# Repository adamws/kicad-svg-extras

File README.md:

<div align="center">

# kicad-svg-extras

_Generate colored SVG files from KiCad PCB files with advanced styling options._

</div>

## Motivation

The `kicad-svg-extras` tool extends KiCad's built-in SVG export capabilities by adding support for custom net colors, CSS-based styling, and advanced color management. While `kicad-cli` provides basic SVG export, this tool respects per-net color settings defined in your PCB project and offers flexible styling options for web integration.

<table>
    <tr>
        <td colspan="2" align="center"></td>
    </tr>
    <tr>
        <td style="width:50%" align="center"><b>kicad-svg-extras</b></td>
        <td style="width:50%" align="center"><b>kicad-cli pcb export svg</b></td>
    </tr>
    <tr>
        <td align="center"></td>
        <td align="center"></td>
    </tr>
</table>

## Features

1. 🎨 **Color-Aware SVG Generation**
    - **Project Color Integration**: Automatically reads and applies net colors from your KiCad project file
    - **Custom Color Override**: Set specific colors for individual nets via command line or JSON configuration
1. 🌐 **Web-Ready CSS Styling**
    - **CSS Class Generation**: Generate SVGs with CSS classes for each net
    - **Metadata Export**: Export CSS class mappings for easy integration
    - **[Live Interactive Demo](https://adamws.github.io/kicad-svg-extras/)**: Try the web features online
1. ⚙️ **Extra Options**
    - **Fit-to-Content**: Automatic canvas sizing based on board edges
    - **Zone Control**: Option to include or exclude copper zones
    - **Background Customization**: Set custom background colors instead of transparent backgrounds

## Installation

### Recommended: Using pipx (Preferred)

[pipx](https://pipx.pypa.io/) is the recommended way to install Python CLI tools.
It installs the tool in an isolated environment while making it globally available:

```bash
pipx install git+https://github.com/adamws/kicad-svg-extras.git
```

For one-time runs use [uvx](https://docs.astral.sh/uv/concepts/tools/):

```bash
uvx --from git+https://github.com/adamws/kicad-svg-extras.git kicad-svg-extras --help
```

**Requirements:**
- KiCad (with Python bindings)
- Python 3.8+

The tool automatically detects and imports KiCad's `pcbnew` module from common installation locations,
so it works in isolated environments without special configuration.

### Custom KiCad Installation Path

If KiCad is installed in a non-standard location, you can specify the path to the pcbnew module
using the `KICAD_PCBNEW_PATH` environment variable:

```bash
export KICAD_PCBNEW_PATH="/path/to/kicad/python/site-packages"
kicad-svg-extras --output board.svg board.kicad_pcb
```

When this environment variable is set, the tool will use it exclusively and will not fall back
to automatic discovery if the path is invalid.

## Usage

<table>
<tr>
<th colspan="2"><b>Basic Usage - Project Colors</b></th>
</tr>
<tr>
<td>

Generate an SVG using colors defined in your KiCad project:

```bash
kicad-svg-extras --output board.svg board.kicad_pcb
```

This automatically:
- Detects the corresponding `.kicad_pro` file
- Applies net colors from the project's `net_colors` settings
- Processes default layers (F.Cu, B.Cu)

</td>
<td>

</td>
</tr>
<tr>
<th colspan="2"><b>Custom Net Colors</b></th>
</tr>
<tr>
<td>

Override specific net colors from the command line
and via `color.json` definition.

```bash
kicad-svg-extras --output board.svg --layers "B.Cu" \
  --ignore-project-colors \
  --net-color "VCC:#fabd2f" --colors colors.json \
  board.kicad_pcb
```

**Supported color formats:**
- Hex: `#FF0000`, `#f00`
- RGB: `rgb(255,0,0)`
- Named: `red`, `green`, `blue`

**colors.json example:**

```json
{
  "net_colors": {
    "N$*": "#b8bb26",
    "VCC": "black",
    "GND": "gray"
  }
}
```

Net names in both `--net-color` and `--colors` json file support wildcards.

</td>
<td>

</td>
</tr>
<tr>
<th colspan="2"><b>CSS Mode for Web Integration</b></th>
</tr>
<tr>
<td>

Generate web-ready SVGs with CSS classes:

```bash
kicad-svg-extras --output board.svg \
  --ignore-project-colors \
  --use-css-classes \
  --export-metadata metadata.json \
  board.kicad_pcb
```

**Creates:**
- **board.svg**: SVG with CSS classes like `.net-gnd-f-cu`
- **metadata.json**: Net-to-CSS mappings

</td>
<td>

</b>
**[Live Interactive Demo](https://adamws.github.io/kicad-svg-extras/)**

</td>
</tr>
</table>

## Command Line Reference

**Basic Syntax:** `kicad-svg-extras -o OUTPUT_FILE [OPTIONS] PCB_FILE`

<table>
<tr>
<th colspan="2"><b>Required Arguments</b></th>
</tr>
<tr>
<td><code>PCB_FILE</code></td>
<td>Input KiCad PCB file (<code>.kicad_pcb</code>)</td>
</tr>
<tr>
<td><code>-o, --output OUTPUT_FILE</code></td>
<td>Output SVG file path</td>
</tr>
<tr>
<th colspan="2"><b>Color Configuration</b></th>
</tr>
<tr>
<td><code>--net-color NET_NAME:COLOR</code></td>
<td>Set color for specific net. Format: <code>net_name:color</code>. Can be used multiple times. Supports hex (<code>#FF0000</code>), RGB (<code>rgb(255,0,0)</code>), or named colors (<code>red</code>).</td>
</tr>
<tr>
<td><code>--colors CONFIG_FILE</code></td>
<td>JSON file with net name to color mapping</td>
</tr>
<tr>
<td><code>--ignore-project-colors</code></td>
<td>Ignore net colors defined in the KiCad project file</td>
</tr>
<tr>
<td><code>-t, --theme THEME_NAME</code></td>
<td>Color theme to use (defaults to PCB editor settings if theme not found)</td>
</tr>
<tr>
<th colspan="2"><b>Layer Selection</b></th>
</tr>
<tr>
<td><code>--layers LAYERS</code></td>
<td>Comma-separated list of KiCad layer names to process (e.g., <code>F.Cu,B.Cu,In1.Cu,In2.Cu</code> or <code>F.Cu,F.SilkS,Edge.Cuts</code>). Default: <code>F.Cu,B.Cu</code></td>
</tr>
<tr>
<th colspan="2"><b>Output Options</b></th>
</tr>
<tr>
<td><code>--use-css-classes</code></td>
<td>Use CSS classes for styling instead of hardcoded colors. Generates individual SVG per net (slower) but allows easy color customization via CSS. Classes: <code>.net-&lt;name&gt; { fill: color; }</code></td>
</tr>
<tr>
<td><code>--export-metadata METADATA_FILE</code></td>
<td>Export net name to CSS class mapping metadata to JSON file. Only useful with <code>--use-css-classes</code>. Contains mapping of actual net names to their CSS class names for integration purposes.</td>
</tr>
<tr>
<td><code>--fit-to-content {none,all,edges_only}</code></td>
<td>Control how bounding box is calculated: <code>none</code> disables fitting (keeps original canvas), <code>all</code> uses all PCB components, <code>edges_only</code> uses only board edges (default)</td>
</tr>
<tr>
<td><code>--no-background</code></td>
<td>Do not add a background to the output SVGs</td>
</tr>
<tr>
<td><code>--background-color BACKGROUND_COLOR</code></td>
<td>Background color for the output SVGs (default: <code>#FFFFFF</code>)</td>
</tr>
<tr>
<th colspan="2"><b>PCB Content Options</b></th>
</tr>
<tr>
<td><code>--skip-zones</code></td>
<td>Skip drawing zones in the output SVGs</td>
</tr>
<tr>
<th colspan="2"><b>Development & Debugging</b></th>
</tr>
<tr>
<td><code>--keep-intermediates</code></td>
<td>Keep intermediate files for debugging</td>
</tr>
<tr>
<td><code>--log-level {DEBUG,INFO,WARNING,ERROR,CRITICAL}</code></td>
<td>Set the logging level (default: INFO)</td>
</tr>
</table>

**Examples**

```bash
# Basic usage with project colors
kicad-svg-extras --output board.svg board.kicad_pcb
# Custom net colors
kicad-svg-extras --output board.svg --net-color 'GND:green' --net-color 'VCC:red' board.kicad_pcb
# Wildcard net patterns
kicad-svg-extras --output board.svg --net-color 'SIGNAL*:blue' board.kicad_pcb
# Using color configuration file
kicad-svg-extras --output board.svg --colors colors.json board.kicad_pcb
# CSS mode for web integration
kicad-svg-extras --output board.svg --use-css-classes --export-metadata metadata.json board.kicad_pcb
# Custom layers and background
kicad-svg-extras --output board.svg --layers "F.Cu,F.SilkS,Edge.Cuts" --background-color "#000000" board.kicad_pcb
# Fit to board edges only, skip zones
kicad-svg-extras --output board.svg --fit-to-content edges_only --skip-zones board.kicad_pcb
```

## How It Works

### Color Priority System

Colors are resolved using a clear priority hierarchy:

1. CLI Arguments (Highest Priority)
2. JSON Configuration File
3. KiCad Project File
4. KiCad Theme Defaults (Lowest Priority)

### Processing Workflow

1. **Net Analysis**: Extract all nets from the PCB and determine which layers they appear on
2. **Color Resolution**: Apply the color priority system to assign final colors
3. **PCB Splitting**: Create filtered PCB files for each net group (same color nets are processed together)
4. **SVG Generation**: Use KiCad's plotting API to generate individual SVGs
5. **Color Application**: Apply colors either as direct fill attributes or CSS classes
6. **Layer Merging**: Combine all layers in the correct stacking order

## Development

### Running Tests

```bash
# Unit tests (no KiCad's pcbnew module required)
hatch run test-unit
# Functional tests (requires KiCad's pcbnew module)
hatch run test-functional
```

## Disclaimer

This project has been mostly AI generated using [claude-code](https://github.com/anthropics/claude-code).

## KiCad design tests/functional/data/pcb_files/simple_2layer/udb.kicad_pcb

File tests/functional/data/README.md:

# Test Data Directory

This directory contains test data for functional testing of kicad-svg-extras.

## Structure

```
tests/data/
├── pcb_files/          # KiCad PCB files for testing
│   ├── simple_2layer/  # Basic 2-layer board
│   ├── simple_4layer/  # Basic Multi-layer board
├── config_files/       # Color configuration files
│   ├── basic_colors.json      # Simple net color mappings
│   └── advanced_nets.json     # Complex patterns and wildcards
└── README.md          # This file
```

## PCB Files (To be added)

PCB test files should be organized by complexity and layer count:

- **simple_2layer/**: Basic 2-layer board
  - origins in [kle2netlist](https://github.com/adamws/kle2netlist)
- **simple_4layer/**: Basic Multi-layer board
  - copied from [UDB-C-EZM](https://github.com/Unified-Daughterboard/UDB-C-EZM)

## Configuration Files

### basic_colors.json
Simple color mappings for common nets:
- GND: Red (#FF0000)
- VCC: Blue (#0000FF)
- 3V3: Green (#00FF00)
- Plus wildcard patterns for DATA*, CLK*, etc.

### advanced_nets.json
Complex configuration with:
- Named colors (red, blue, green)
- Wildcard patterns (USB_*, SPI_*, I2C_*)
- KiCad project format compatibility

## Usage

These files are used by functional tests in `tests/functional/` to:
1. Generate SVG outputs with various CLI options
2. Compare against human-verified reference files
3. Test different layer combinations and color schemes
4. Validate error handling with invalid inputs

## Adding New Test Data

When adding new PCB files:
1. Place in appropriate subdirectory by complexity
2. Include a brief description of the board purpose
3. Generate reference SVG files using current tool version
4. Manually verify reference outputs before committing
5. Add corresponding test cases in functional tests

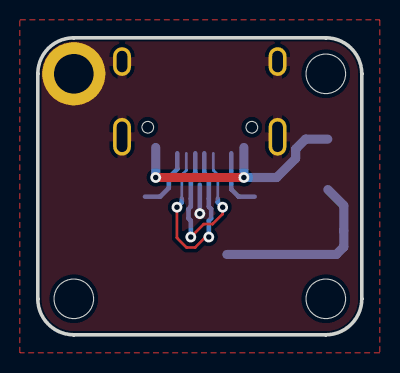
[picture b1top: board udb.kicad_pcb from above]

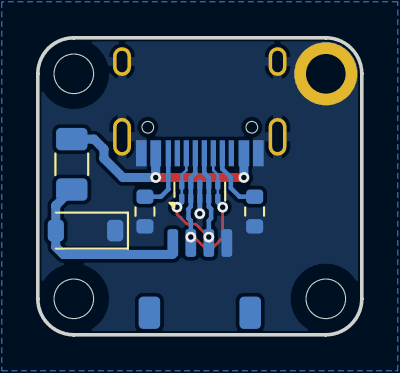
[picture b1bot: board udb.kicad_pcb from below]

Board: 2 copper layers, 18.0 x 16.5 mm, 11 parts (7 on the bottom side), 7 nets.

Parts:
D1: D_Zener; D_SOD-123
F1: Polyfuse; Fuse_1206_3216Metric
H1: MountingHole_Pad; MountingHole_2.2mm_M2_Pad_TopBottom
H2, H3, H4: MountingHole; MountingHole_2.2mm_M2
J1: USB_C_Receptacle_USB2.0_14P; USB_C_Receptacle_HRO_TYPE-C-31-M-12
J2: Conn_01x04; JST_SH_SM04B-SRSS-TB_1x04-1MP_P1.00mm_Horizontal
R1, R2: 5.1k; R_0603_1608Metric
U1: TPD4E05U06DQA; USON-10_2.5x1.0mm_P0.5mm

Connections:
D+: J1.A6, J1.B6, J2.3, U1.1, U1.4, U1.7, U1.10
D-: J1.A7, J1.B7, J2.2, U1.2, U1.5, U1.6, U1.9
GND: D1.1, H1.1, J1.A1, J1.A12, J1.B1, J1.B12, J1.S1, J2.4, R1.2, R2.2, U1.3, U1.8
unnamed: J1.A5, R1.1
unnamed: J1.B5, R2.1
VBUS: F1.1, J1.A4, J1.A9, J1.B4, J1.B9
VCC: D1.2, F1.2, J2.1

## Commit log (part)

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2025-07-19 Remove coverage upload stage
2025-07-19 Bump softprops/action-gh-release from 1 to 2
    Bumps [softprops/action-gh-release](https://github.com/softprops/action-gh-release) from 1 to 2.
    - [Release notes](https://github.com/softprops/action-gh-release/releases)
    - [Changelog](https://github.com/softprops/action-gh-release/blob/master/CHANGELOG.md)
    - [Commits](https://github.com/softprops/action-gh-release/compare/v1...v2)
    ---
    updated-dependencies:
2025-07-19 Bump actions/setup-python from 4 to 5
    Bumps [actions/setup-python](https://github.com/actions/setup-python) from 4 to 5.
    - [Release notes](https://github.com/actions/setup-python/releases)
    - [Commits](https://github.com/actions/setup-python/compare/v4...v5)
    ---
    updated-dependencies:
    - dependency-name: actions/setup-python
2025-07-19 Move color handling to separate file
2025-07-19 Simplify CLI interface
2025-07-19 Remove unused methods
2025-07-19 Remove most classes and use function approach instead
2025-07-19 Remove `pcbnew` mocks
2025-07-19 Remove coverage tool setup as it is not yet used
2025-07-19 Improve logging format
2025-07-19 Fix ruff error
2025-07-19 Remove HSL support
2025-07-19 Stop using `setup-python` as it conflicts with using system's pcbnew
2025-07-19 Fix handling kicad_pro file without `net_colors` defined
2025-07-19 Do not do any other modification than color change for intermediate svgs
2025-07-19 Allow to define net color directly with CLI arguments
2025-07-19 Fix setting background rectangle size
2025-07-19 Remove copper DRAWINGS when processing nets
2025-07-19 Add `--use-css-classes` option
2025-07-19 Refactor `pcb_net_filter`
2025-07-19 Assert that size and viewbox for all intermediate svgs is equal
2025-07-19 Fix copyright
2025-07-20 Add pre-commit configuration
2025-07-20 Add coverage measurement
2025-07-20 Add coverage report to step summary
2025-07-20 Adds colored logging for warning and error messages
2025-07-20 Raise exception when loading board fails
2025-07-21 Start tracking development `.justfile`
2025-07-21 Save some output clutter when using just from agent context
2025-07-21 Add html report upload step
2025-07-21 Add minimal `CLAUDE.md`
2025-07-21 Minor `.justfile` changes and specification what agent can do
2025-07-21 Add alias
2025-07-21 Add instruction about writing git commit messages
2025-07-22 Add debug log messages
2025-07-22 Move `tempfile` to pytest's `tmpdir` and do not clean
    pytest will rotate them
2025-07-22 Add `pytest-html` dependency
2025-07-22 Fix misleading `CSS` processing warning
2025-07-22 Allow passing test filter
2025-07-22 Keep intermediate files when testing
2025-07-22 Change example colors definition to make it easier to inspect
2025-07-29 Replace kicad-cli subprocess calls with native pcbnew API
    This commit refactors the SVG generation system to use KiCad's native pcbnew
    Python API instead of subprocess calls to kicad-cli, providing better performance
    and more precise control over the plotting process.
    Key changes:
    - **pcbnew_utils.py**: Added `generate_svg_from_board()` function that uses
    PLOT_CONTROLLER API directly for SVG generation, replacing subprocess calls
2025-07-29 Implement aux origin-based fit-to-content functionality
    This commit introduces KiCad's native aux origin system to replace complex SVG
    post-processing for fit-to-content behavior, providing more accurate coordinate
    system alignment and handling of edge cases like small PCBs.
    Key changes:
    - **pcbnew_utils.py**: Added comprehensive aux origin support with functions:
    - `get_board_bounding_box()`: Calculate consistent bounding box from original PCB
2025-07-29 Add fit-to-content option with edges_only
    This commit introduces a new `--fit-to-content` option that allows
    specifying how the SVG is fitted to its content.
    The following options are available:
    - `none`: No fitting is performed.
    - `all`: The SVG is fitted to all board elements.
    - `edges_only`: The SVG is fitted to the board edges only.
2025-07-29 Add svg sanitization stage which removes empty groups
2025-07-29 Started working on README.md
2025-07-29 Minor comment updates
2025-07-30 Unify demo behaviour
2025-07-30 Run semantic comparison of generated svg against reference
2025-07-30 Add interactive web demo for CSS-based SVG exports
    This commit introduces a new interactive web-based demo to showcase the
    power of the CSS-enabled SVG output.
    The demo, located in the `demo/` directory, provides an interactive
    experience for exploring PCB designs, featuring:
    - **Net Highlighting:** Clicking on a net in the list highlights all its
    corresponding elements on the SVG canvas, using a KiCad-like selection
2025-07-30 Add option to ignore project defined colors
2025-07-30 Add link to project website
2025-07-31 Add `--theme` option
2025-07-31 Add examples to readme and deploy demo website
2025-07-31 Bump actions/configure-pages from 4 to 5
    Bumps [actions/configure-pages](https://github.com/actions/configure-pages) from 4 to 5.
    - [Release notes](https://github.com/actions/configure-pages/releases)
    - [Commits](https://github.com/actions/configure-pages/compare/v4...v5)
    ---
    updated-dependencies:
    - dependency-name: actions/configure-pages
2025-07-31 Add test status badge
2025-07-31 Create LICENSE
2025-08-01 Suggest installing with `pipx` or running with `uvx`
2025-08-01 Add tests on Windows
2025-08-11 Bump actions/checkout from 4 to 5
    Bumps [actions/checkout](https://github.com/actions/checkout) from 4 to 5.
    - [Release notes](https://github.com/actions/checkout/releases)
    - [Changelog](https://github.com/actions/checkout/blob/main/CHANGELOG.md)
    - [Commits](https://github.com/actions/checkout/compare/v4...v5)
    ---
    updated-dependencies:
2025-08-26 Bump actions/upload-pages-artifact from 3 to 4
    Bumps [actions/upload-pages-artifact](https://github.com/actions/upload-pages-artifact) from 3 to 4.
    - [Release notes](https://github.com/actions/upload-pages-artifact/releases)
    - [Commits](https://github.com/actions/upload-pages-artifact/compare/v3...v4)
    ---
    updated-dependencies:
    - dependency-name: actions/upload-pages-artifact
2025-09-08 Bump actions/setup-python from 5 to 6
    Bumps [actions/setup-python](https://github.com/actions/setup-python) from 5 to 6.
    - [Release notes](https://github.com/actions/setup-python/releases)
    - [Commits](https://github.com/actions/setup-python/compare/v5...v6)
    ---
    updated-dependencies:
    - dependency-name: actions/setup-python
2025-10-27 Bump actions/upload-artifact from 4 to 5
    Bumps [actions/upload-artifact](https://github.com/actions/upload-artifact) from 4 to 5.
    - [Release notes](https://github.com/actions/upload-artifact/releases)
    - [Commits](https://github.com/actions/upload-artifact/compare/v4...v5)
    ---
    updated-dependencies:
    - dependency-name: actions/upload-artifact
2025-11-24 Bump actions/checkout from 4 to 6
    Bumps [actions/checkout](https://github.com/actions/checkout) from 4 to 6.
    - [Release notes](https://github.com/actions/checkout/releases)
    - [Changelog](https://github.com/actions/checkout/blob/main/CHANGELOG.md)
    - [Commits](https://github.com/actions/checkout/compare/v4...v6)
    ---
    updated-dependencies:
2025-12-15 Bump actions/upload-artifact from 4 to 6
    Bumps [actions/upload-artifact](https://github.com/actions/upload-artifact) from 4 to 6.
    - [Release notes](https://github.com/actions/upload-artifact/releases)
    - [Commits](https://github.com/actions/upload-artifact/compare/v4...v6)
    ---
    updated-dependencies:
    - dependency-name: actions/upload-artifact
2026-03-09 Bump actions/upload-artifact from 4 to 7
    Bumps [actions/upload-artifact](https://github.com/actions/upload-artifact) from 4 to 7.
    - [Release notes](https://github.com/actions/upload-artifact/releases)
    - [Commits](https://github.com/actions/upload-artifact/compare/v4...v7)
    ---
    updated-dependencies:
    - dependency-name: actions/upload-artifact
2026-03-30 Bump actions/configure-pages from 5 to 6
    Bumps [actions/configure-pages](https://github.com/actions/configure-pages) from 5 to 6.
    - [Release notes](https://github.com/actions/configure-pages/releases)
    - [Commits](https://github.com/actions/configure-pages/compare/v5...v6)
    ---
    updated-dependencies:
    - dependency-name: actions/configure-pages
2026-03-30 Bump actions/deploy-pages from 4 to 5
    Bumps [actions/deploy-pages](https://github.com/actions/deploy-pages) from 4 to 5.
    - [Release notes](https://github.com/actions/deploy-pages/releases)
    - [Commits](https://github.com/actions/deploy-pages/compare/v4...v5)
    ---
    updated-dependencies:
    - dependency-name: actions/deploy-pages
2026-04-13 Bump softprops/action-gh-release from 2 to 3
    Bumps [softprops/action-gh-release](https://github.com/softprops/action-gh-release) from 2 to 3.
    - [Release notes](https://github.com/softprops/action-gh-release/releases)
    - [Changelog](https://github.com/softprops/action-gh-release/blob/master/CHANGELOG.md)
    - [Commits](https://github.com/softprops/action-gh-release/compare/v2...v3)
    ---
    updated-dependencies:
2026-04-20 Bump actions/upload-pages-artifact from 3 to 5
    Bumps [actions/upload-pages-artifact](https://github.com/actions/upload-pages-artifact) from 3 to 5.
    - [Release notes](https://github.com/actions/upload-pages-artifact/releases)
    - [Commits](https://github.com/actions/upload-pages-artifact/compare/v3...v5)
    ---
    updated-dependencies:
    - dependency-name: actions/upload-pages-artifact
